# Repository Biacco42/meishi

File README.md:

# Meishi

**Meishi - The micro macro keyboard.**

The 4-key micro macro keyboard for self-made keyboard beginners.

# Parts

- **1** Meishi PCB
- **1** 5V/16MHz Pro Micro compatible boards
- **4** 1N4148 diodes
- **4** [Switches of your choice](https://mechanicalkeyboards.com/shop/index.php?l=product_list&c=107)
- **1** Tact switch
- **4** Rubber pads

## Mount the Diodes

Meishi PCB is symmetrical. The side with the logo is the top.
**Double check your work**. Black lines must be facing the square pad.

## Mount switches

Mount switches on the top side of the PCB.

## Mount the Pro Micro

Mount the Pro Micro on the top side of the PCB with the Pro Micro's USB facing up. (Please refer to the image)

## Attach rubber pads

Attach the rubber pads on the bottom side of the PCB.

## Flash QMK Firmware

QMK firmware for Meishi is available in [this repo on the meishi branch](https://github.com/Biacco42/qmk_firmware/tree/master/keyboards/meishi).
This readme document does not cover how to build QMK. Please refer to the [QMK documents](https://docs.qmk.fm/).

Connect the keyboard to the PC via USB and run the following:

```
$ make meishi:default:avrdude
```

It will build and try to flash your firmware. Follow the instructions that require to reset the Pro Micro.

This process may require elevated privileges.

## You're all done!

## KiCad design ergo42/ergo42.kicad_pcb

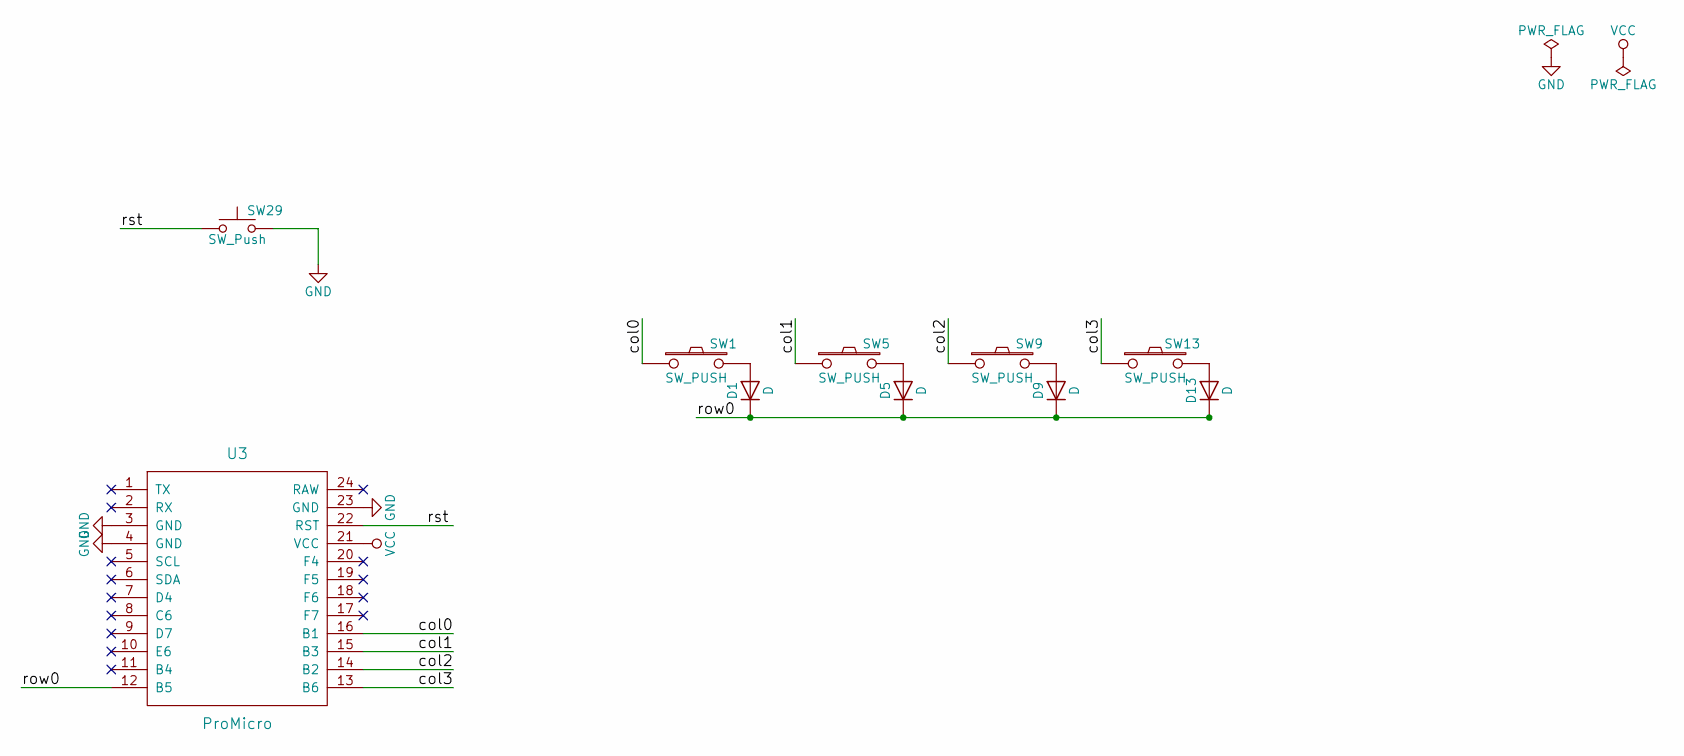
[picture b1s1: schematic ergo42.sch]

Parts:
D1, D5, D9, D13: D; Diode_SMD_THT
SW1, SW5, SW9, SW13: SW_PUSH; key_switch
SW29: SW_Push; tact_switch
U3: ProMicro

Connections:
/col0: SW1.1, U3.16 (B1)
/col1: SW5.1, U3.15 (B3)
/col2: SW9.1, U3.14 (B2)
/col3: SW13.1, U3.13 (B6)
/row0: D1.1 (K), D5.1 (K), D9.1 (K), D13.1 (K), U3.12 (B5)
/rst: SW29.1, U3.22 (RST)
GND: SW29.2, U3.3 (GND), U3.4 (GND), U3.23 (GND)
unnamed: D1.2 (A), SW1.2
unnamed: D5.2 (A), SW5.2
unnamed: D9.2 (A), SW9.2
unnamed: D13.2 (A), SW13.2
VCC: U3.21 (VCC)

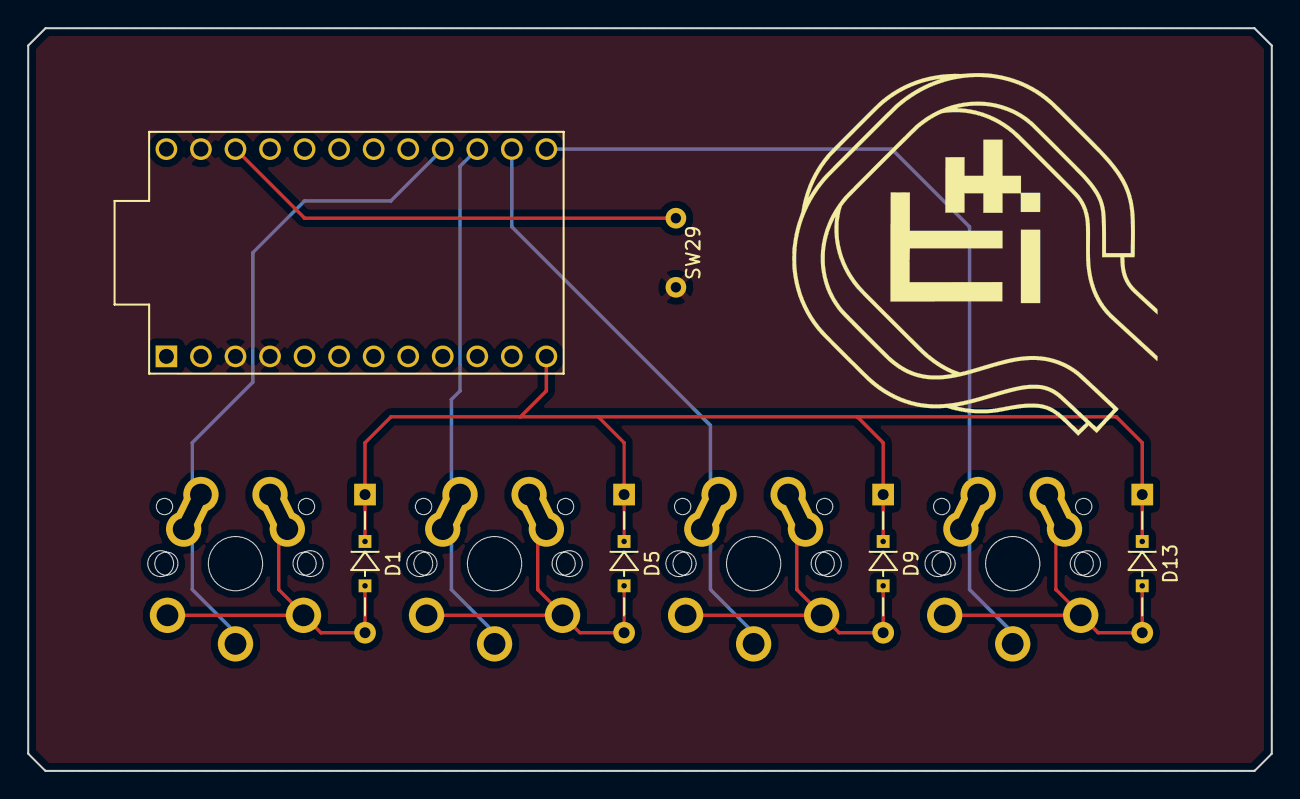
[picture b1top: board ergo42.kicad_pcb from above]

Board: 2 copper layers, 91.4 x 54.6 mm, 10 parts (0 on the bottom side), 11 nets.

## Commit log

2017-12-21 Make meishi switch
2017-12-21 Implement
2018-01-20 Add readme image
2018-01-20 Update LICENSE
2018-01-20 Remove needless case
2018-01-20 Rename file names
2018-01-20 Add initial document
2019-03-19 readme link to QMK changed, readme text changed
